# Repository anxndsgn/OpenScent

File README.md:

# OpenScent
OpenScent is an olfactory interface development board that releases scents by spraying and writing code using Arduino.

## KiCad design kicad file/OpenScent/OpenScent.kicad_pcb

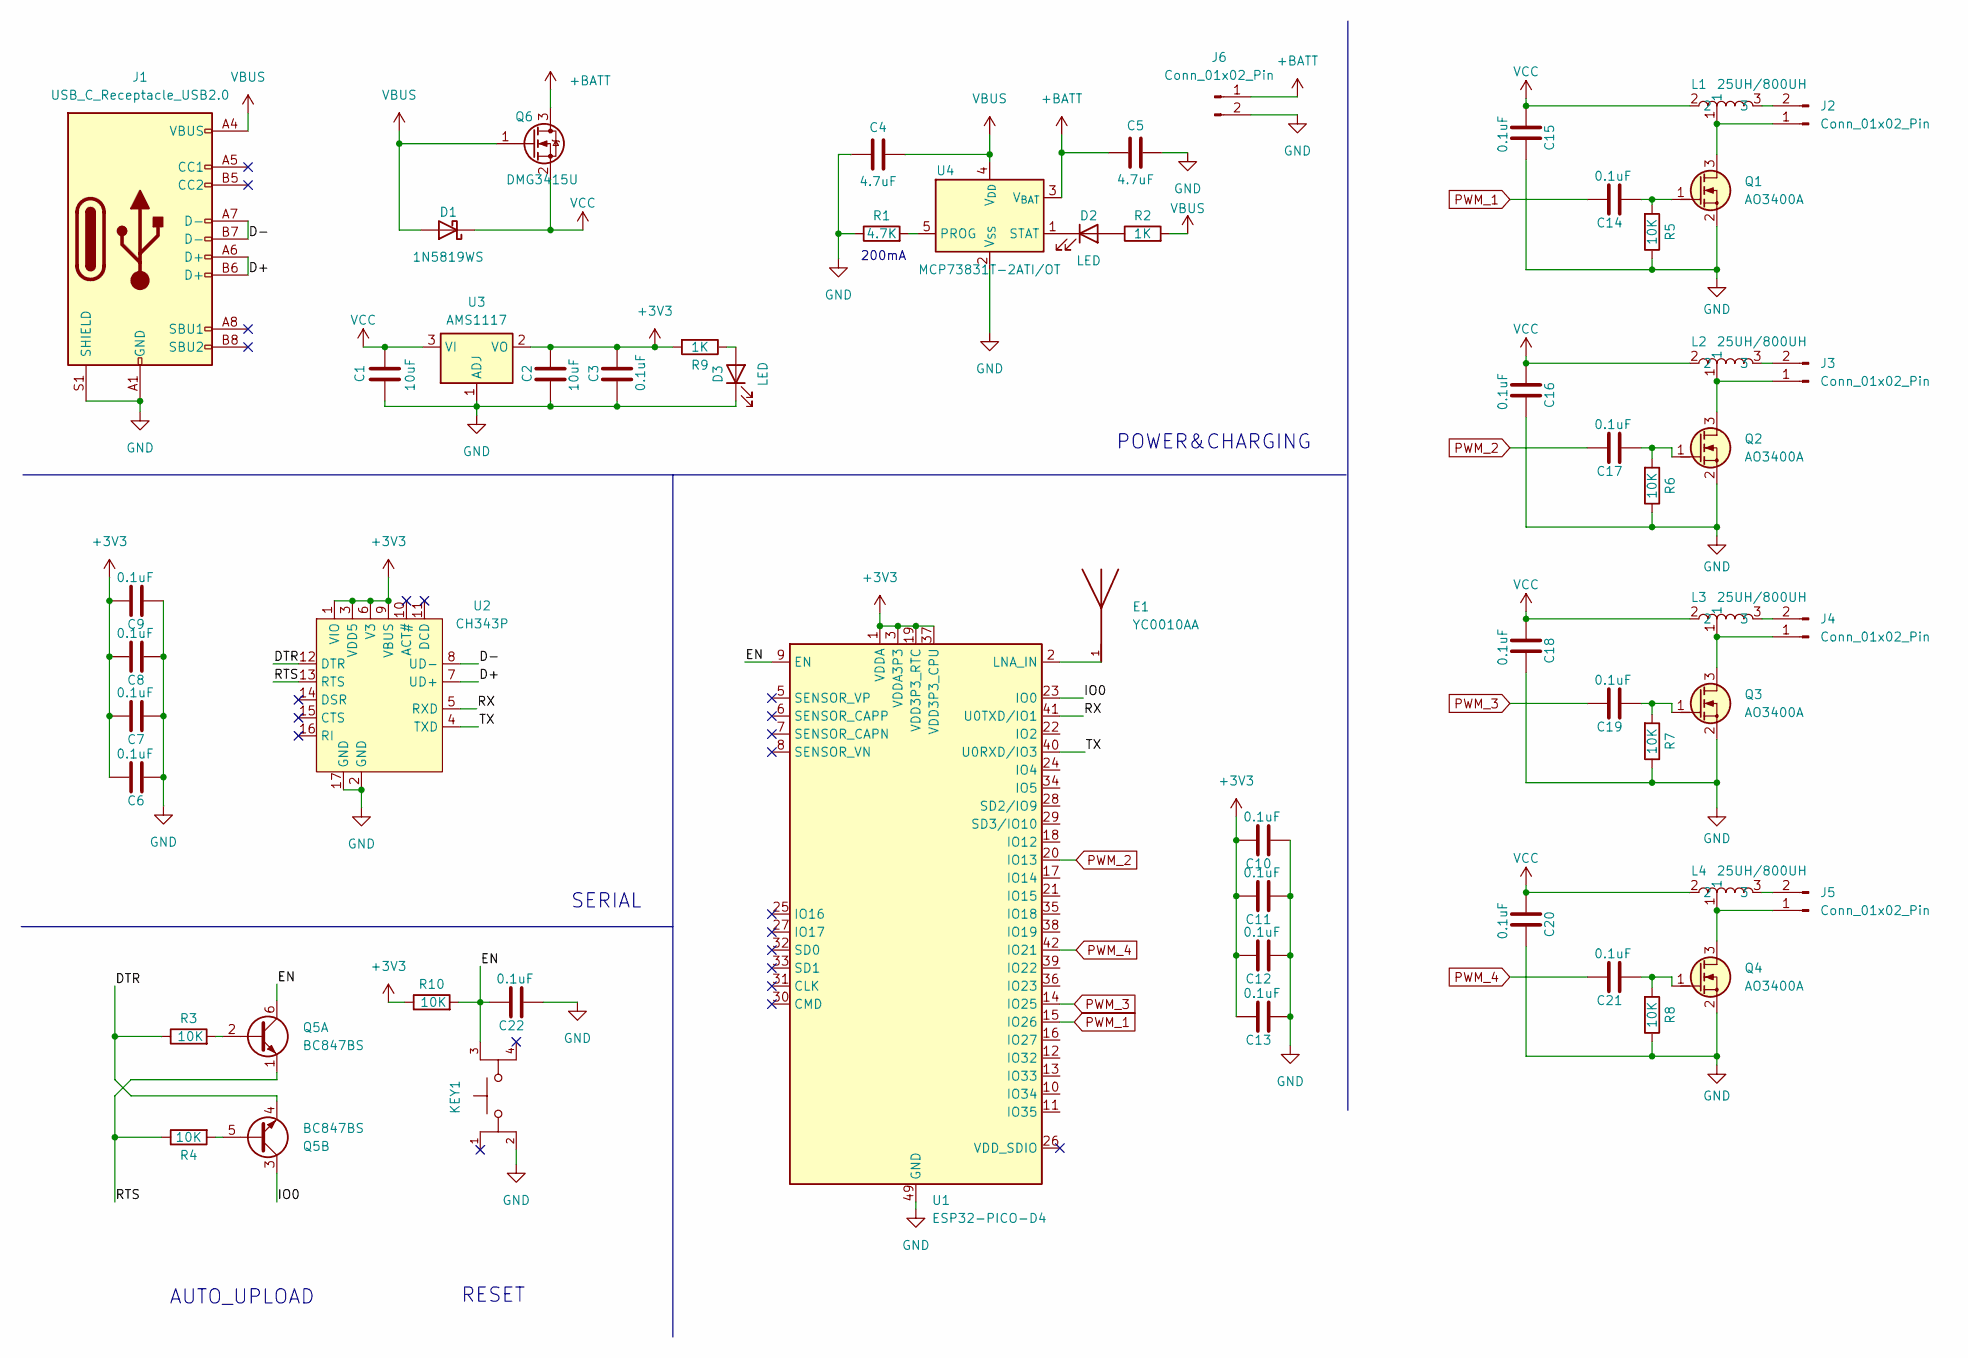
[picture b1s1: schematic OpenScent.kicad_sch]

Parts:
C1, C2: 10uF; C_0603_1608Metric_Pad1.08x0.95mm_HandSolder
C3, C6, C7, C8, C9, C10, C11, C12, C13, C14, C15, C16, C17, C18, C19, C20, C21, C22: 0.1uF; C_0603_1608Metric_Pad1.08x0.95mm_HandSolder
C4, C5: 4.7uF; C_0603_1608Metric_Pad1.08x0.95mm_HandSolder
D1: 1N5819WS; D_SOD-323; LCSC Part # C191023
D2, D3: LED; LED_0603_1608Metric
E1: YC0010AA; XCVR_YC0010AA; PARTREV 1.1
J1: USB_C_Receptacle_USB2.0; USB_C_Receptacle_G-Switch_GT-USB-7010ASV
J2, J3, J4, J5, J6: Conn_01x02_Pin; JST_PH_B2B-PH-K_1x02_P2.00mm_Vertical
KEY1: SW_TL3365AF180QG; PARTREV A
L1, L2, L3, L4: 25UH/800UH; 3 pin inductor
Q1, Q2, Q3, Q4: AO3400A; SOT-23
Q5: BC847BS; SOT-363_SC-70-6
Q6: DMG3415U; SOT-23; LCSC Part # C7202986
R1: 4.7K; R_0603_1608Metric
R2, R9: 1K; R_0603_1608Metric
R3, R4, R5, R6, R7, R8, R10: 10K; R_0603_1608Metric
U1: ESP32-PICO-D4; QFN-48-1EP_7x7mm_P0.5mm_EP5.3x5.3mm
U2: CH343P; QFN-16-1EP_3x3mm_P0.5mm_EP1.9x1.9mm; LCSC Part # C2846043
U3: AMS1117; SOT-89-3
U4: MCP73831T-2ATI/OT; SOT-23-5; LCSC Part # C14879

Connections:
+3V3: C2.1, C3.1, C6.1, C7.1, C8.1, C9.1, C10.1, C11.1, C12.1, C13.1, R9.2, R10.1, U1.1 (VDDA), U1.3 (VDDA3P3), U1.4 (VDDA3P3), U1.19 (VDD3P3_RTC), U1.37 (VDD3P3_CPU), U1.43 (VDDA), U1.46 (VDDA), U2.1 (VIO), U2.3 (VDD5), U2.6 (V3), U2.9 (VBUS), U3.2 (VO)
+BATT: C5.2, J6.1, Q6.3 (D), U4.3 (V_{BAT})
/D+: J1.A6 (D+), J1.B6 (D+), U2.7 (UD+)
/D-: J1.A7 (D-), J1.B7 (D-), U2.8 (UD-)
/DTR: Q5.4 (E2), R3.1, U2.12 (DTR)
/EN: C22.1, KEY1.3, Q5.6 (C1), R10.2, U1.9 (EN)
/IO0: Q5.3 (C2), U1.23 (IO0)
/RTS: Q5.1 (E1), R4.1, U2.13 (RTS)
/RX: U1.41 (U0TXD/IO1), U2.5 (RXD)
/TX: U1.40 (U0RXD/IO3), U2.4 (TXD)
GND: C1.2, C2.2, C3.2, C4.2, C5.1, C6.2, C7.2, C8.2, C9.2, C10.2, C11.2, C12.2, C13.2, C15.1, C16.1, C18.1, C20.1, C22.2, D3.1 (K), J1.A1 (GND), J1.A12 (GND), J1.B1 (GND), J1.B12 (GND), J1.S1 (SHIELD), J6.2, KEY1.2, Q1.2 (S), Q2.2 (S), Q3.2 (S), Q4.2 (S), R1.1, R5.1, R6.1, R7.1, R8.1, U1.49 (GND), U2.2 (GND), U2.17 (GND), U3.1 (ADJ), U4.2 (V_{SS})
unnamed: D2.2 (A), R2.1
unnamed: D2.1 (K), U4.1 (STAT)
unnamed: D3.2 (A), R9.1
unnamed: J2.1, L1.1, Q1.3 (D)
unnamed: J2.2, L1.3
unnamed: J3.1, L2.1, Q2.3 (D)
unnamed: J3.2, L2.3
unnamed: J4.1, L3.1, Q3.3 (D)
unnamed: J4.2, L3.3
unnamed: J5.1, L4.1, Q4.3 (D)
unnamed: J5.2, L4.3
unnamed: C14.2, Q1.1 (G), R5.2
unnamed: C17.2, Q2.1 (G), R6.2
unnamed: C19.2, Q3.1 (G), R7.2
unnamed: C21.2, Q4.1 (G), R8.2
unnamed: Q5.2 (B1), R3.2
unnamed: Q5.5 (B2), R4.2
unnamed: E1.1, U1.2 (LNA_IN)
unnamed: R1.2, U4.5 (PROG)
PWM_1: C14.1, U1.15 (IO26)
PWM_2: C17.1, U1.20 (IO13)
PWM_3: C19.1, U1.14 (IO25)
PWM_4: C21.1, U1.42 (IO21)
VBUS: C4.1, D1.2 (A), J1.A4 (VBUS), J1.A9 (VBUS), J1.B4 (VBUS), J1.B9 (VBUS), Q6.1 (G), R2.2, U4.4 (V_{DD})
VCC: C1.1, C15.2, C16.2, C18.2, C20.2, D1.1 (K), L1.2, L2.2, L3.2, L4.2, Q6.2 (S), U3.3 (VI)

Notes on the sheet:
AUTO_UPLOAD
POWER&CHARGING
SERIAL
200mA
RESET

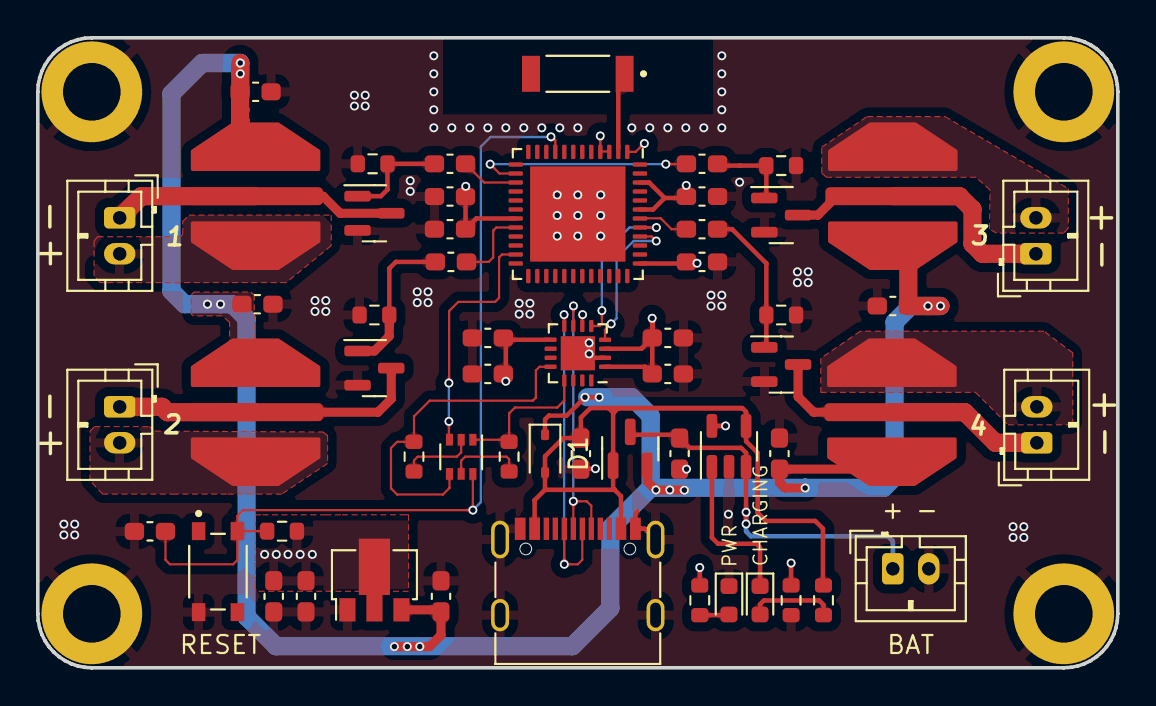
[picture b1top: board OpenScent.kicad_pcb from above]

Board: 4 copper layers, 60.0 x 35.0 mm, 57 parts (0 on the bottom side), 36 nets.

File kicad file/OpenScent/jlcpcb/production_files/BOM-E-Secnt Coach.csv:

Comment,Designator,Footprint,LCSC
MCP73831T-2ATI/OT,U4,SOT-23-5,C14879
1N5819WS,D1,D_SOD-323,C191023
ESP32-PICO-D4,U1,QFN-48-1EP_7x7mm_P0.5mm_EP5.3x5.3mm,C193707
CH343P,U2,QFN-16-1EP_3x3mm_P0.5mm_EP1.9x1.9mm,C2846043
0.1uF,"C10,C11,C12,C13,C14,C15,C16,C17,C18,C19,C20,C21,C3,C6,C7,C8,C9",C_0603_1608Metric_Pad1.08x0.95mm_HandSolder,C30926
DMG3415U,Q6,SOT-23,C7202986
Conn_01x02_Pin,J4,JST_PH_B2B-PH-K_1x02_P2.00mm_Vertical,
AMS1117,U3,SOT-89-3,
Conn_01x02_Pin,J3,JST_PH_B2B-PH-K_1x02_P2.00mm_Vertical,
25UH/800UH,L2,3 pin inductor,
LED,D3,LED_0603_1608Metric,
USB_C_Receptacle_USB2.0,J1,USB_C_Receptacle_G-Switch_GT-USB-7010ASV,
AO3400A,Q2,SOT-23,
1K,R2,R_0603_1608Metric,
10K,R5,R_0603_1608Metric,
10K,R7,R_0603_1608Metric,
10K,R3,R_0603_1608Metric,
AO3400A,Q1,SOT-23,
Conn_01x02_Pin,J5,JST_PH_B2B-PH-K_1x02_P2.00mm_Vertical,
10K,R6,R_0603_1608Metric,
AO3400A,Q3,SOT-23,
25UH/800UH,L1,3 pin inductor,
BC847BS,Q5,SOT-363_SC-70-6,
AO3400A,Q4,SOT-23,
25UH/800UH,L4,3 pin inductor,
4.7uF,C4,C_0603_1608Metric_Pad1.08x0.95mm_HandSolder,
4.7uF,C5,C_0603_1608Metric_Pad1.08x0.95mm_HandSolder,
10K,R8,R_0603_1608Metric,
25UH/800UH,L3,3 pin inductor,
4.7K,R1,R_0603_1608Metric,
10K,R4,R_0603_1608Metric,
Conn_01x02_Pin,J2,JST_PH_B2B-PH-K_1x02_P2.00mm_Vertical,
1K,R9,R_0603_1608Metric,
10uF,C2,C_0603_1608Metric_Pad1.08x0.95mm_HandSolder,
LED,D2,LED_0603_1608Metric,
Conn_01x02_Pin,J6,JST_PH_B2B-PH-K_1x02_P2.00mm_Vertical,
10uF,C1,C_0603_1608Metric_Pad1.08x0.95mm_HandSolder,
YC0010AA,E1,XCVR_YC0010AA,
10K,R10,R_0603_1608Metric,
0.1uF,C22,C_0603_1608Metric_Pad1.08x0.95mm_HandSolder,
~,KEY1,SW_TL3365AF180QG,

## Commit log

2024-01-07 organized files and update readme
